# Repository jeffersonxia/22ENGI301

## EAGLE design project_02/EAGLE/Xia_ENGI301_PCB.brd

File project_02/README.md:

This PCB is designed to serve as a light switch and dimmer for Neopixels. 

The neopixels are controlled with a M0 trinket from Adafruit.

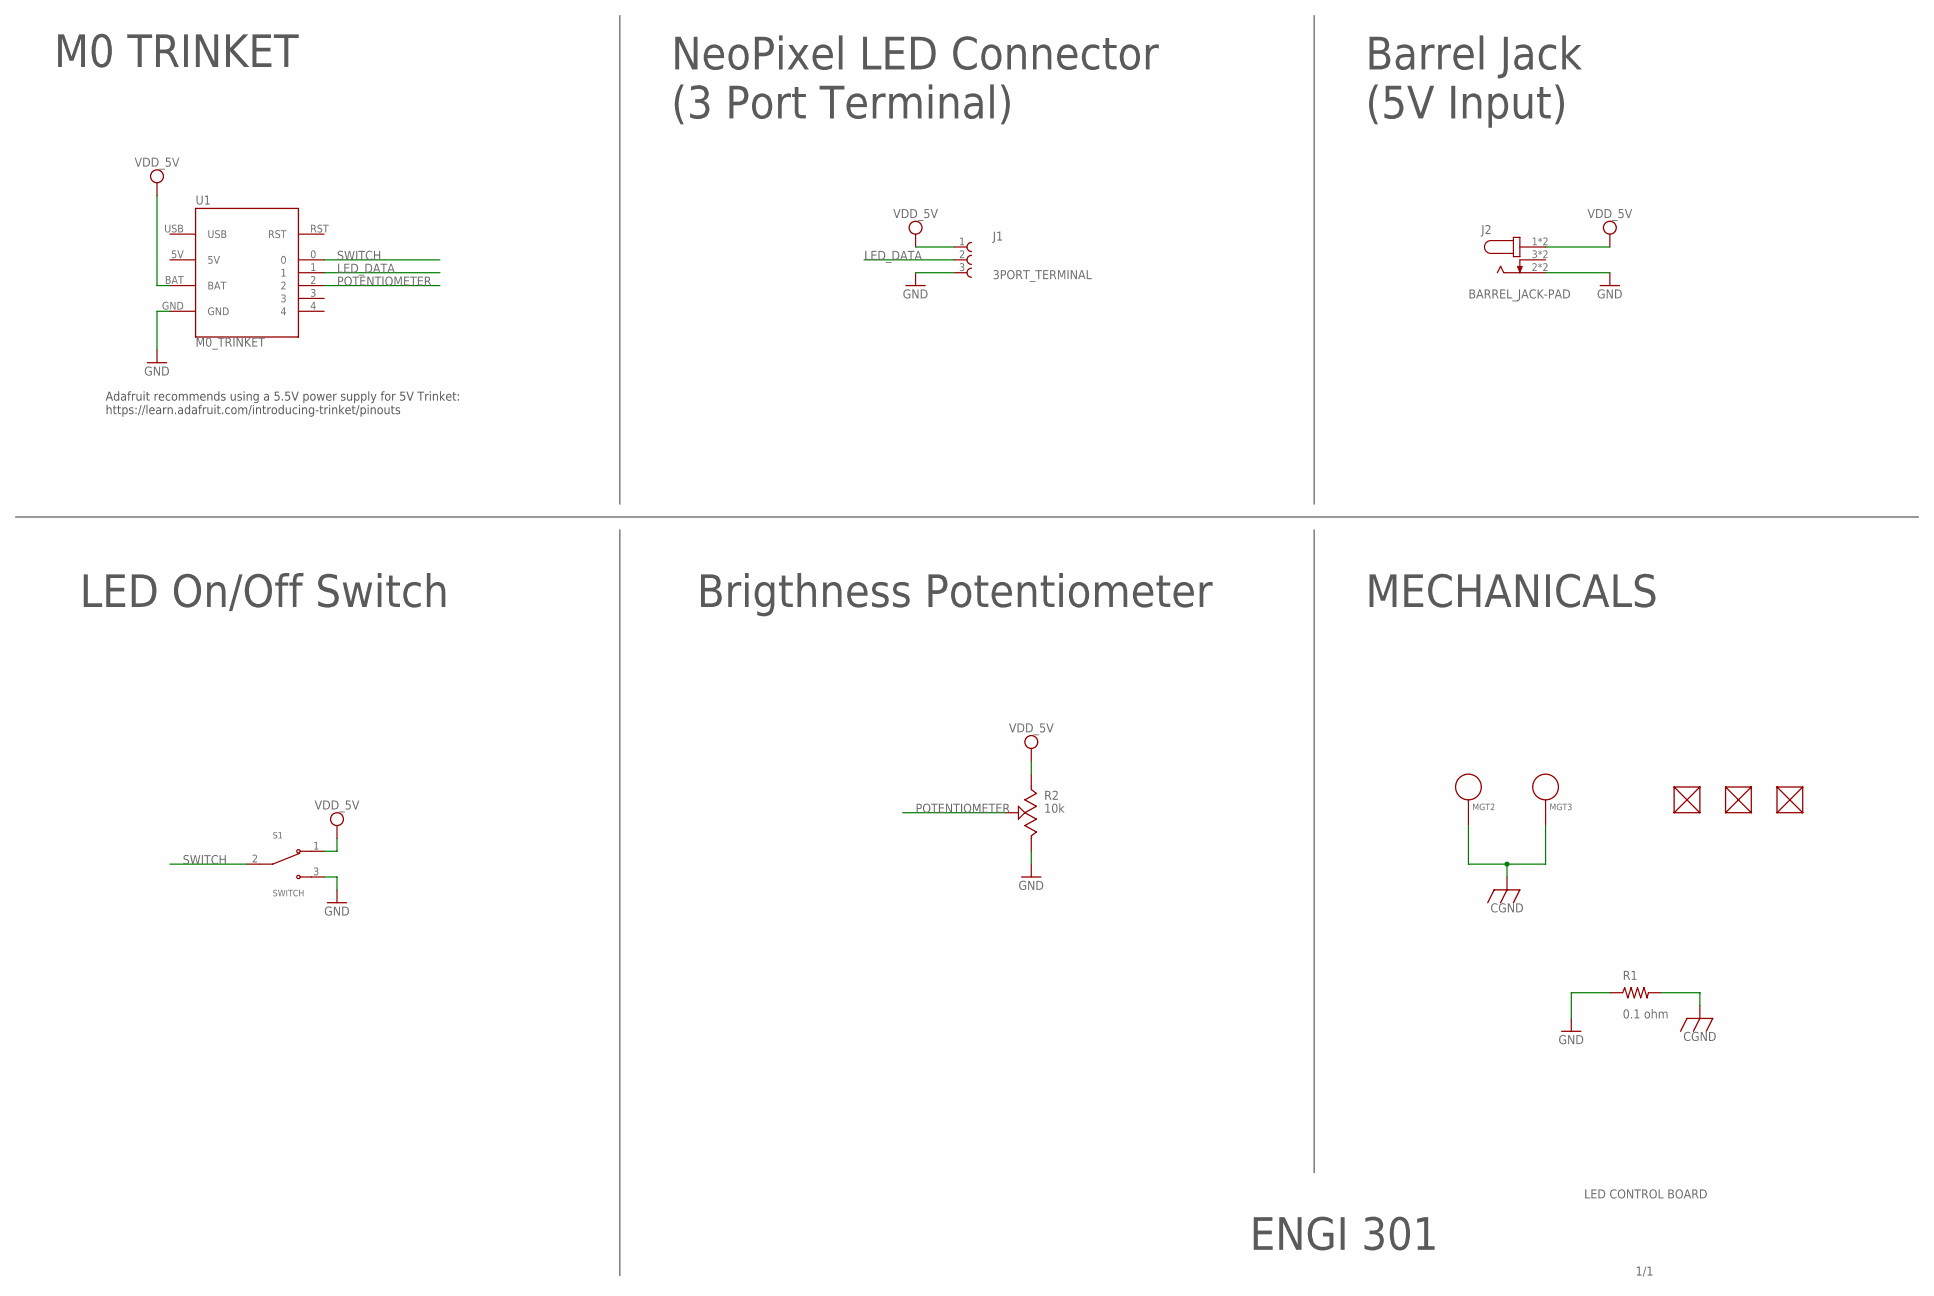
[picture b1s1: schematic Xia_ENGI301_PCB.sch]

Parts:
FUD1, FUD2, FUD3: FIDUCIAL; FIDUCIAL_40MIL
J1: 3PORT_TERMINAL
J2: BARREL_JACK-PAD; BARREL_JACK
MGT2, MGT3: MOUNTING_HOLE
R1: 0.1 ohm; 0207/10
R2: 10k; POTENTIOMETER
S1: SWITCH
U1: M0_TRINKET

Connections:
5V: U1.5V
CGND: MGT2.P$1, MGT3.P$1, R1.2
GND: J1.3, J2.2, J2.2_B (2), R1.1, R2.3, S1.3, U1.GND
LED_DATA: J1.2, U1.1
POTENTIOMETER: R2.2, U1.2
SWITCH: S1.2, U1.0
VDD_5V: J1.1, J2.1, J2.1_B (1), R2.1, S1.1, U1.BAT

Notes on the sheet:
1/1
M0 TRINKET
NeoPixel LED Connector (3 Port Terminal)
Barrel Jack (5V Input)
LED On/Off Switch
Brigthness Potentiometer
ENGI 301
LED CONTROL BOARD
MECHANICALS
Adafruit recommends using a 5.5V power supply for 5V Trinket: https://learn.adafruit.com/introducing-trinket/pinouts

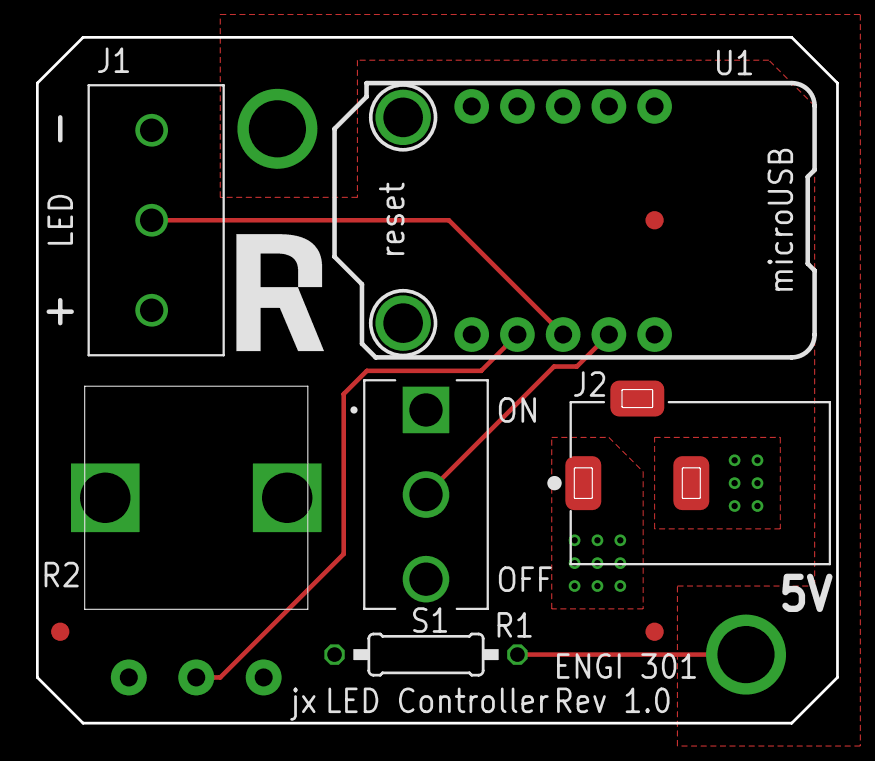
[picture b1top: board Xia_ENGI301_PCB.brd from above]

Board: 4 copper layers, 44.5 x 38.1 mm, 11 parts (0 on the bottom side), 6 nets.

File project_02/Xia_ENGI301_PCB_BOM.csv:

"Qty";"Value";"Device";"Package";"Parts";"Description";"AVAILABILITY";"DESCRIPTION";"MANUFACTURER";"MF";"MP";"PACKAGE";"PART_REV";"PRICE";"PURCHASE-URL";"STANDARD";
"1";"0.1 ohm";"R-US_0207/10";"0207/10";"R1";"RESISTOR, American symbol";"";"";"";"";"";"";"";"";"";"";
"1";"10k";"POTENTIOMETER";"POTENTIOMETER";"R2";"";"";"";"";"";"";"";"";"";"";"";
"1";"3PORT_TERMINAL";"3PORT_TERMINAL";"3PORT_TERMINAL";"J1";"SERIE 1377 - 5.00 MM - HORIZONTAL CABLE ENTRY WITH  PRESSURE CLAMP - GLOW WIRE PLASTIC - WR-TBL";"In Stock";" 3 Position Wire to Board Terminal Block Horizontal with Board 0.197 (5.00mm) Through Hole ";"";"Wurth Elektronik";"691137710003";"None";"";"None";"https://pricing.snapeda.com/search/part/691137710003/?ref=eda";"";
"1";"BARREL_JACK-PAD";"BARREL_JACK-PAD";"BARREL_JACK";"J2";"2.5 mm Center Pin, 5.0 A, Right Angle, Through Hole, Tapered Pins, Dc Power Jack Connector";"";"";"CUI INC";"";"";"";"1.02";"";"";"Manufacturer recommendations";
"3";"FIDUCIAL";"FIDUCIAL";"FIDUCIAL_40MIL";"FUD1, FUD2, FUD3";"";"";"";"";"";"";"";"";"";"";"";
"1";"M0_TRINKET";"M0_TRINKET";"M0_TRINKET";"U1";"";"";"";"";"";"";"";"";"";"";"";
"2";"MOUNTING_HOLE";"MOUNTING_HOLE";"MOUNTING_HOLE";"MGT2, MGT3";"Chassis Mounting Hole w/GND connection ability";"";"";"";"";"";"";"";"";"";"";
"1";"SWITCH";"SWITCH";"SWITCH";"S1";"Toggle Switch SPDT Through Hole  Check availability";"In Stock";" Toggle Switch SPDT Through Hole ";"";"E-Switch";"100SP1T1B4M2QE";"None";"";"None";"https://pricing.snapeda.com/search/part/100SP1T1B4M2QE/?ref=eda";"";

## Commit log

2022-01-29 Updating README.md
    Update for assignment 2
2022-01-29 Updating README.md
2022-02-14 Assignment #4 Question 1 Commit
2022-02-14 Adding comments
2022-02-16 Uploading Split Flap Code
2022-04-05 Adding Project 01
2022-04-05 Adding files via upload
2022-04-05 Adding README
2022-05-02 Updating Project 2 Files
